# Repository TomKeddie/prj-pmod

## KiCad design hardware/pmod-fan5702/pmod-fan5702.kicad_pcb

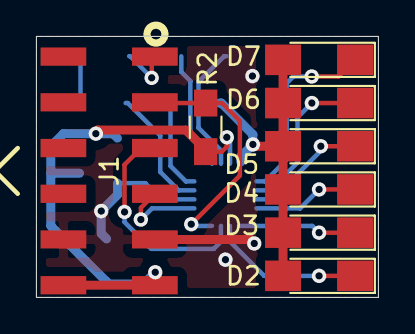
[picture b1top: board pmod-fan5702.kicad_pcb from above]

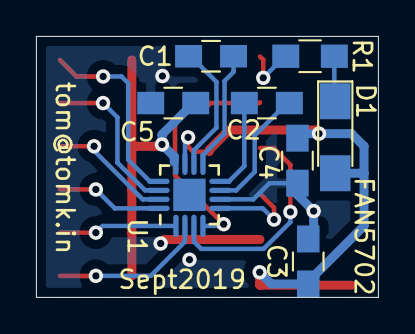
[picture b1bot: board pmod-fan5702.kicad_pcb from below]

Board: 2 copper layers, 19.0 x 14.5 mm, 16 parts (8 on the bottom side), 18 nets.

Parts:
C1, C2, C5: 1uF; C_0805_HandSoldering
C3: 10uF; C_0805_HandSoldering
C4: 0.1uF; C_0805_HandSoldering
D1, D2, D3, D4, D5, D6, D7: LED; LED_1206_HandSoldering
J1: PMOD-2x6-MALE; 2X6_SMD_RA_PLUG
R1: 220R; R_0805_HandSoldering
R2: 10k; R_0805_HandSoldering
U1: FAN5702UM; QFN-16-1EP_3x3mm_Pitch0.5mm_HS

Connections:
+3V3: C3.1, C4.1, D1.2, J1.6, J1.12, R2.1, U1.11
/C1+: C1.1, U1.10
/C1-: C1.2, U1.9
/C2+: C2.2, U1.8
/C2-: C2.1, U1.7
/D1A: D2.1, U1.2
/D2A: D3.1, U1.1
/D3: D4.1, U1.16
/D4: D5.1, U1.15
/D5: D6.1, U1.14
/D6: D7.1, U1.13
/EN: J1.2, R2.2, U1.4
/LED: J1.1, R1.2
/SCL: J1.3, U1.3
/SDA: J1.4, U1.5
/VOUT: C5.2, D2.2, D3.2, D4.2, D5.2, D6.2, D7.2, U1.12
GND: C3.2, C4.2, C5.1, J1.5, J1.11, U1.6
unnamed: D1.1, R1.1

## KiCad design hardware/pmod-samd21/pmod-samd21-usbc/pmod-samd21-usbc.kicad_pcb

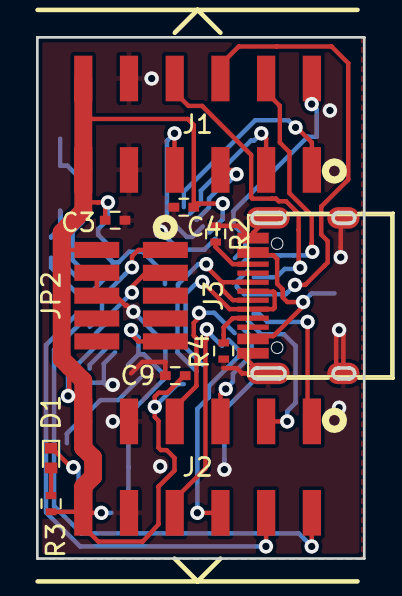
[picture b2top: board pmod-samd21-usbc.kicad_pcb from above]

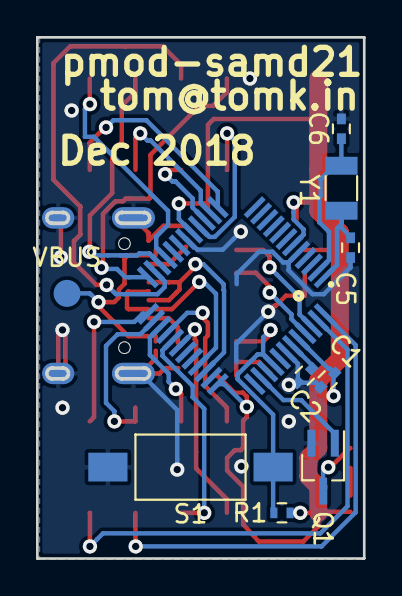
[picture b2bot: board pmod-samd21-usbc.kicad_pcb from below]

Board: 2 copper layers, 18.2 x 29.0 mm, 21 parts (10 on the bottom side), 32 nets.

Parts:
C1, C2, C3, C4, C9: 0.1uF; C_0402
C5, C6: 15pF; C_0402
D1: LED; LED_0402
J1: PMOD-2x6-MALE; 2X6_SMD_RA_PLUG
J2: PMOD-2x6-FEMALE; 2X6_SMD_RA_SOCKET
J3: USB_C_Receptacle_USB2.0; USB_C_Receptacle_GT-USB-7010
JP2: CORTEX_DEBUGPTH; CONN_1.27_2x5
Q1: 2N7002PW; SOT-323_SC-70_Handsoldering
R1: 10K; R_0402
R2, R4: 5.1k; R_0402
R3: 330; R_0402
S1: SWITCH-MOMENTARY-2SMD; SW_SPST_SMD_2PIN_3.5x6.0
TP1: VBUS; Measurement_Point_Round-SMD-Pad_Small
U1: ATSAMD21G-A; QFP50P900X900X120-48N
Y1: 32.768kHz; Crystal_SMD_3215-2pin_3.2x1.5mm

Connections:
+3V3: C1.1, C3.1, C4.1, C9.1, J1.6, J1.12, J2.6, J2.12, JP2.1, R1.2, R3.2, U1.6, U1.17, U1.36, U1.44
/BLUE_LED: Q1.1, U1.38
/SER0_0: J1.1, U1.13
/SER0_1: J1.2, U1.14
/SER0_2: J1.3, U1.15
/SER0_3: J1.4, U1.16
/SER1_0: J2.1, U1.25
/SER1_1: J2.2, U1.26
/SER1_2: J2.3, U1.27
/SER1_3: J2.4, U1.28
/SER2_0: J1.7, U1.21
/SER2_1: J1.8, U1.22
/SER2_2: J1.9, U1.23
/SER2_3: J1.10, U1.24
/SER5_0: J2.7, U1.47
/SER5_1: J2.8, U1.48
/SER5_2: J2.9, U1.29
/SER5_3: J2.10, U1.30
/SWCLK: JP2.4, U1.45
/SWDIO: JP2.2, U1.46
/USB_D+: J3.A6, J3.B6, U1.34
/USB_D-: J3.A7, J3.B7, U1.33
/~RESET: JP2.10, R1.1, S1.1, U1.40
GND: C1.2, C2.2, C3.2, C4.2, C5.1, C6.2, C9.2, J1.5, J1.11, J2.5, J2.11, J3.A1, J3.A12, J3.B1, J3.B12, J3.S1, JP2.3, JP2.5, Q1.2, R2.1, R4.1, S1.2, U1.5, U1.18, U1.35, U1.42
unnamed: C2.1, U1.43
unnamed: C5.2, U1.1, Y1.2
unnamed: C6.1, U1.2, Y1.1
unnamed: D1.1, Q1.3
unnamed: D1.2, R3.1
unnamed: J3.A5, R4.2
unnamed: J3.B5, R2.2
VBUS: J3.A4, J3.A9, J3.B4, J3.B9, TP1.1

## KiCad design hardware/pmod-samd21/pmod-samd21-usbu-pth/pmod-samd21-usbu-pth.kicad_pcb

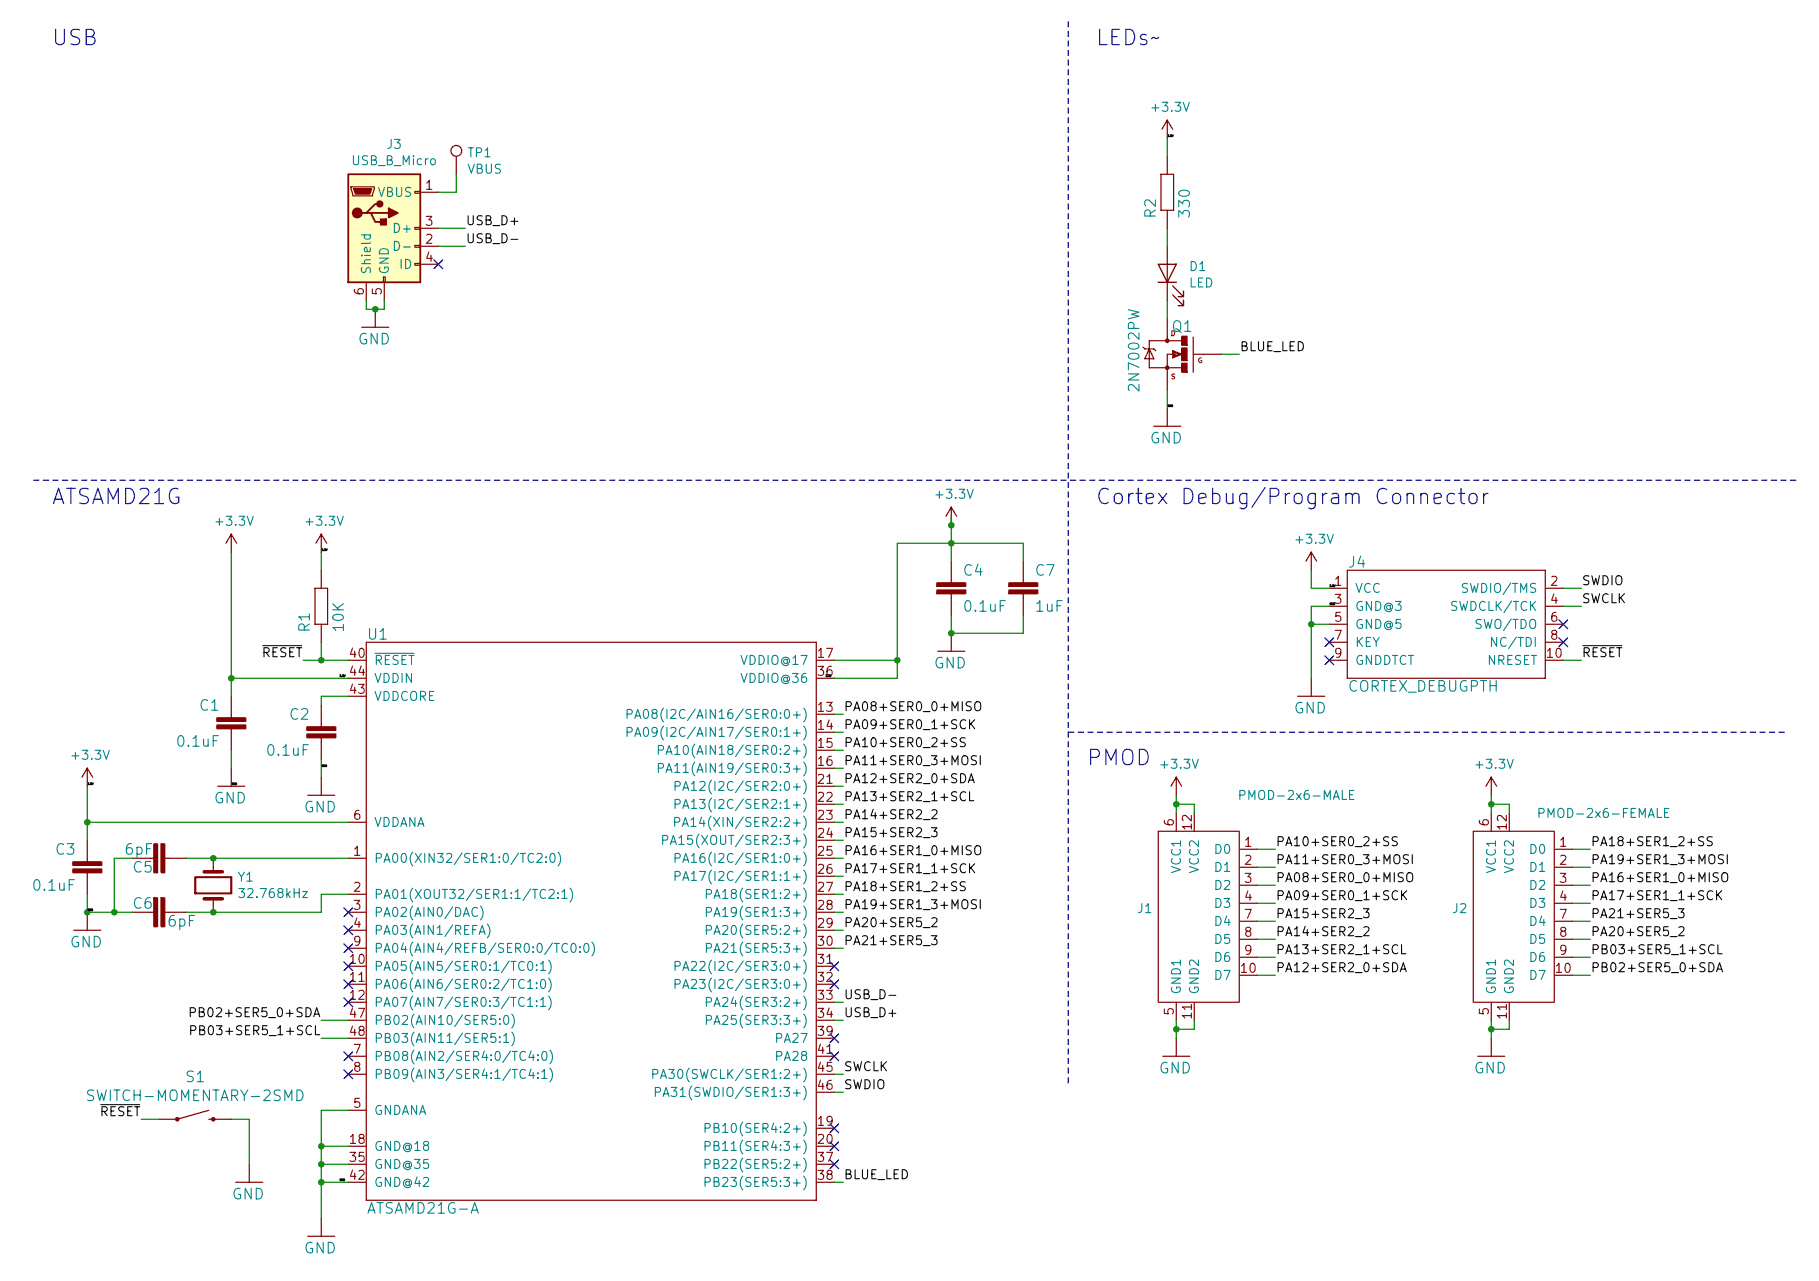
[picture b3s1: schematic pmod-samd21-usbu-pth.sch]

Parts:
C1, C2, C3, C4: 0.1uF; C_0402
C5, C6: 6pF; C_0402
C7: 1uF; C_0402
D1: LED; LED_0402
J1: PMOD-2x6-MALE; 2X6_SMD_RA_PLUG
J2: PMOD-2x6-FEMALE; 2X6_SMD_RA_SOCKET
J3: USB_B_Micro; USB_MICRO_TAOBAO_SMD_PTH
J4: CORTEX_DEBUGPTH; CONN_1.27_2x5
Q1: 2N7002PW; SOT-323_SC-70_Handsoldering
R1: 10K; R_0402
R2: 330; R_0402
S1: SWITCH-MOMENTARY-2SMD; SW_SPST_SMD_2PIN_3.5x6.0
TP1: VBUS; Measurement_Point_Round-SMD-Pad_Small
U1: ATSAMD21G-A; QFP50P900X900X120-48N
Y1: 32.768kHz; Crystal_SMD_3215-2pin_3.2x1.5mm

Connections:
+3V3: C1.1, C3.1, C4.1, C7.1, J1.6 (VCC1), J1.12 (VCC2), J2.6 (VCC1), J2.12 (VCC2), J4.1 (VCC), R1.2, R2.2, U1.6 (VDDANA), U1.17 (VDDIO@17), U1.36 (VDDIO@36), U1.44 (VDDIN)
/BLUE_LED: Q1.1 (G), U1.38 (PB23(SER5:3+))
/PA08+SER0_0+MISO: J1.3 (D2), U1.13 (PA08(I2C/AIN16/SER0:0+))
/PA09+SER0_1+SCK: J1.4 (D3), U1.14 (PA09(I2C/AIN17/SER0:1+))
/PA10+SER0_2+SS: J1.1 (D0), U1.15 (PA10(AIN18/SER0:2+))
/PA11+SER0_3+MOSI: J1.2 (D1), U1.16 (PA11(AIN19/SER0:3+))
/PA12+SER2_0+SDA: J1.10 (D7), U1.21 (PA12(I2C/SER2:0+))
/PA13+SER2_1+SCL: J1.9 (D6), U1.22 (PA13(I2C/SER2:1+))
/PA14+SER2_2: J1.8 (D5), U1.23 (PA14(XIN/SER2:2+))
/PA15+SER2_3: J1.7 (D4), U1.24 (PA15(XOUT/SER2:3+))
/PA16+SER1_0+MISO: J2.3 (D2), U1.25 (PA16(I2C/SER1:0+))
/PA17+SER1_1+SCK: J2.4 (D3), U1.26 (PA17(I2C/SER1:1+))
/PA18+SER1_2+SS: J2.1 (D0), U1.27 (PA18(SER1:2+))
/PA19+SER1_3+MOSI: J2.2 (D1), U1.28 (PA19(SER1:3+))
/PA20+SER5_2: J2.8 (D5), U1.29 (PA20(SER5:2+))
/PA21+SER5_3: J2.7 (D4), U1.30 (PA21(SER5:3+))
/PB02+SER5_0+SDA: J2.10 (D7), U1.47 (PB02(AIN10/SER5:0))
/PB03+SER5_1+SCL: J2.9 (D6), U1.48 (PB03(AIN11/SER5:1))
/SWCLK: J4.4 (SWDCLK/TCK), U1.45 (PA30(SWCLK/SER1:2+))
/SWDIO: J4.2 (SWDIO/TMS), U1.46 (PA31(SWDIO/SER1:3+))
/USB_D+: J3.3 (D+), U1.34 (PA25(SER3:3+))
/USB_D-: J3.2 (D-), U1.33 (PA24(SER3:2+))
/~RESET: J4.10 (NRESET), R1.1, S1.1, U1.40 (~RESET~)
GND: C1.2, C2.2, C3.2, C4.2, C5.1, C6.2, C7.2, J1.5 (GND1), J1.11 (GND2), J2.5 (GND1), J2.11 (GND2), J3.5 (GND), J3.6 (Shield), J4.3 (GND@3), J4.5 (GND@5), Q1.2 (S), S1.2, U1.5 (GNDANA), U1.18 (GND@18), U1.35 (GND@35), U1.42 (GND@42)
unnamed: C2.1, U1.43 (VDDCORE)
unnamed: C5.2, U1.1 (PA00(XIN32/SER1:0/TC2:0)), Y1.2
unnamed: C6.1, U1.2 (PA01(XOUT32/SER1:1/TC2:1)), Y1.1
unnamed: D1.1 (K), Q1.3 (D)
unnamed: D1.2 (A), R2.1
unnamed: J3.1 (VBUS), TP1.1

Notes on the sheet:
USB
LEDs~~~
Cortex Debug/Program Connector
ATSAMD21G
PMOD

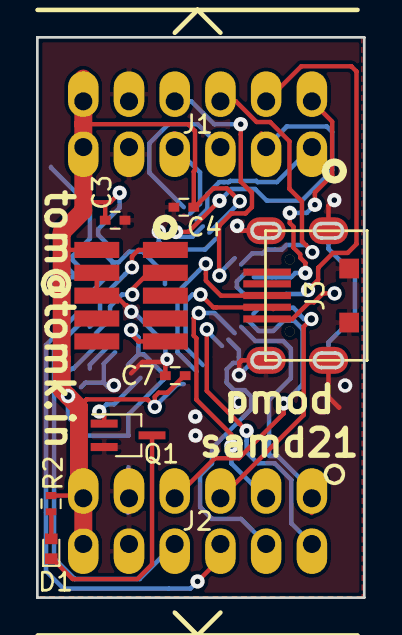
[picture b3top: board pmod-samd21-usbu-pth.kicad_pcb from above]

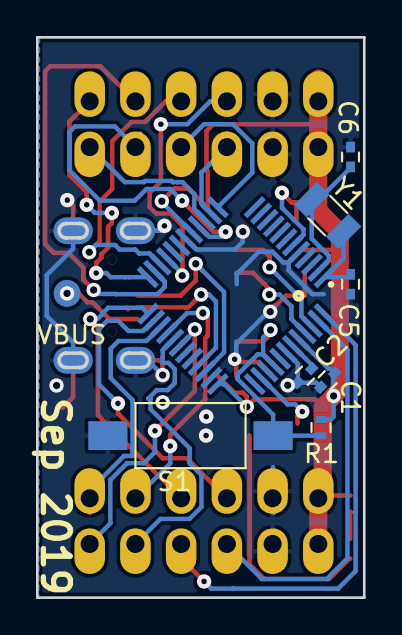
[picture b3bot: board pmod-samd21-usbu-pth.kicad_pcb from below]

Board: 2 copper layers, 18.2 x 31.1 mm, 19 parts (9 on the bottom side), 30 nets.

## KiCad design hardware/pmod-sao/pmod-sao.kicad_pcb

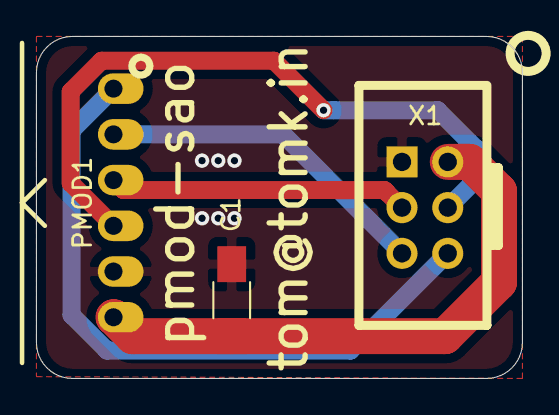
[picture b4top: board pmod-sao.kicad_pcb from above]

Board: 2 copper layers, 27.0 x 19.0 mm, 3 parts (0 on the bottom side), 6 nets.

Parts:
C1: 10uF; C_1206_HandSoldering
PMOD1: PMOD-Device-x1-Type-1-GPIO; PMOD_1X6_PTH_RA_PLUG
X1: Badgelife_sao_connector_v169bis; Badgelife-SAOv169-BADGE-2x3

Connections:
/GPIO1: PMOD1.1, X1.5
/GPIO2: PMOD1.2, X1.6
/SCL: PMOD1.3, X1.4
/SDA: PMOD1.4, X1.3
GND: C1.2, PMOD1.5, X1.2
VCC: C1.1, PMOD1.6, X1.1

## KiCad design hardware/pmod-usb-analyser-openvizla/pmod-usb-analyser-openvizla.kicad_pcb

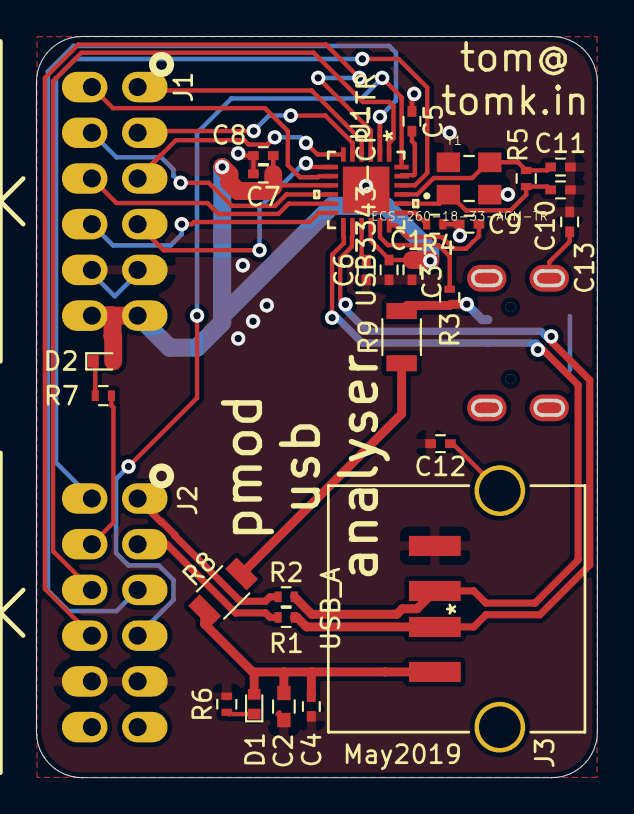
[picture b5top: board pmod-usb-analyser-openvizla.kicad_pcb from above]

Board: 2 copper layers, 31.2 x 41.2 mm, 30 parts (1 on the bottom side), 34 nets.

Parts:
C1, C3, C7, C9: 0.1uF; C_0402
C2: 10uF; C_0603
C4, C5, C6, C8: 1uF; C_0402
C10, C11: 18pF; C_0402
C12, C13: 0.1uF/6.3V; C_0402
D1, D2: LED; LED_0402
J1, J2: PMOD-2x6-MALE; PMOD_2X6_PTH_RA_PLUG
J3: USB_A; 87583-2010BLF
J4: USB_B_Micro; USB_MICRO_TAOBAO_SMD_PTH
R1, R2: 1k; R_0402
R3: 10k; R_0402
R4: 8k06/1%; R_0402
R5: 1M; R_0402
R6: 1K; R_0402
R7: 330R; R_0402
R8, R9: R; R_1206
U1: USB3343-CP-TR
Y1: ECS-260-18-33-AGM-TR; XTAL_ECS-260-18-33-AGM-TR

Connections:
+3V3: C1.1, C3.1, C7.1, C8.1, D2.2, J1.6, J1.12, U1.9, U1.16
/CLKOUT: J2.3, U1.2
/DATA0: J1.1, U1.4
/DATA1: J1.2, U1.5
/DATA2: J1.3, U1.6
/DATA3: J1.4, U1.7
/DATA4: J1.7, U1.8
/DATA5: J1.8, U1.10
/DATA6: J1.9, U1.11
/DATA7: J1.10, U1.12
/DIR: J2.9, U1.1
/ID: C9.1, U1.18
/J3_SHIELD: C12.1, J3.5
/J4_SHIELD: C13.1, J4.6
/NXT: J2.10, U1.3
/RBIAS: R4.2, U1.19
/RESETB: J2.7, U1.22
/STP: J2.4, U1.24
/USB_TAP_DP: J2.1, R2.1
/USER_LED: J2.8, R7.2
/VBUS: C2.1, C4.1, D1.2, J3.1, R8.1
/VBUS1: R8.2, R9.1
/VBUS_SENSE: R3.1, U1.17
/VDD18: C5.1, U1.23
/VDD33: C6.1, U1.15
/X0: C10.1, R5.1, U1.20, Y1.1
/XI: C11.1, R5.2, U1.21, Y1.3
GND: C1.2, C2.2, C3.2, C4.2, C5.2, C6.2, C7.2, C8.2, C9.2, C10.2, C11.2, C12.2, C13.2, J1.5, J1.11, J2.5, J2.11, J3.4, J4.5, R4.1, R6.2, U1.25, Y1.2, Y1.4
unnamed: D1.1, R6.1
unnamed: D2.1, R7.1
unnamed: J2.2, R1.1
USB_DN: J3.2, J4.2, R1.2, U1.14
USB_DP: J3.3, J4.3, R2.2, U1.13
VBUS2: J4.1, R3.2, R9.2

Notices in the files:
parts and their libraries:
Copyright 2016 Accelerated Designs. All rights reserved.
